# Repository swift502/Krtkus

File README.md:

# Krtkus

> [!WARNING]
> Krtkus has been succeeded by [Krteq](https://github.com/swift502/Krteq), a much more complete design that's also easier to build. I recommend you check it out instead!

An extended 5x12 keyboard with 2 extra keys. The design is intended for ortho layouts with a shifted number row, allowing for the placement of the delete and tilde keys above their usual spots. PCBs are designed in Kicad, case in Blender.

- Low profile
    - Kailh Choc V1
    - Gateron KS-27/KS-33
- QMK/VIA compatible
- Tray mount
- 3D printed case with a 7 degree tilt
- 236mm × 122mm × 30mm

Connecting the keyboard to [usevia.app](https://usevia.app) requires manually uploading the [design file](production/krtkus_via.json) in the design tab.

## Parts

- One of the PCBs:
    - [Choc V1](production/pcb_choc_v1)
    - [KS-33](production/pcb_ks_33)
- Case: 
    - [STL file](production/krtkus_case.stl)
- Arduino Pro Micro
- 61 SMD diodes
- 61 switches
- 61 keycaps
- 5 M2x6mm screws

#### Optional:

- 90 degree Micro-USB cable
- Rubber feet

## Room for improvement

- Spacebar stabilizer
- Num/Caps indicators
- LED matrix
- Hotswap version
- Standard USB port orientation
- Protect the MCU against dust

All of the above have been addressed by the successor [Krteq](https://github.com/swift502/Krteq).

## My builds

| Board | Keycaps | Switches | Case | Firmware |
| --- | --- | --- | --- | --- |
|  | MBK Legend Ergo/Ortho | Choc V1 Brown | Black Resin | Caterina |
|  | Keychron LSA ABS | KS-33 Brown | Black Resin | Caterina |
|  | Keychron LSA ABS | KS-33 Red | 9600 Resin | Caterina (Legacy) |
|  | Dell AT101W | KS-33 Banana | [Krtkus Retro](https://github.com/swift502/KrtkusRetro) | Caterina |

## QMK

Standard QMK setup except for `"tap_keycode_delay": 40`, which fixes ignored taps in some games where input scanning is tied to frame rate. To the best of my knowledge, keeping this value above 33ms (30fps) should cover all edge cases.

### Documentation

- `info.json` reference: https://docs.qmk.fm/reference_info_json
- Keycodes: https://docs.qmk.fm/keycodes

### Compiling (Windows)

- Python: https://www.python.org/
- MSYS: https://msys.qmk.fm
- Toolbox: https://qmk.fm/toolbox

Run the compile script:

```sh
python qmk_compile.py
```

### Resetting

Once the firmware is flashed, it provides key combinations to enter bootloader or clear the keyboard's persistent storage.

- <kbd>LShift</kbd> + <kbd>RShift</kbd> + <kbd>B</kbd> - Puts the keyboard into bootloader mode for flashing
- <kbd>LShift</kbd> + <kbd>RShift</kbd> + <kbd>C</kbd> - Clears EEPROM and reverts to the default keymap

## Kicad 8

### Libraries

Below is a list libraries included in the project. These libraries are not licensed under CC0. Please refer to each specific library for licensing details.

- [Scotto Kicad](https://github.com/joe-scotto/scottokeebs/tree/main/Extras/ScottoKicad)
- [MX V2](https://github.com/ai03-2725/MX_V2)
- [Gateron 3D models](https://www.gateron.com/pages/3d)

### Switch grid

| Unit | Offset |
| --- | --- |
| Switch | 19.05 |
| Switch 4 | 4.7625 |
| Switch 16 | 1.190625 |
| Switch 64 | 0.29765625 |

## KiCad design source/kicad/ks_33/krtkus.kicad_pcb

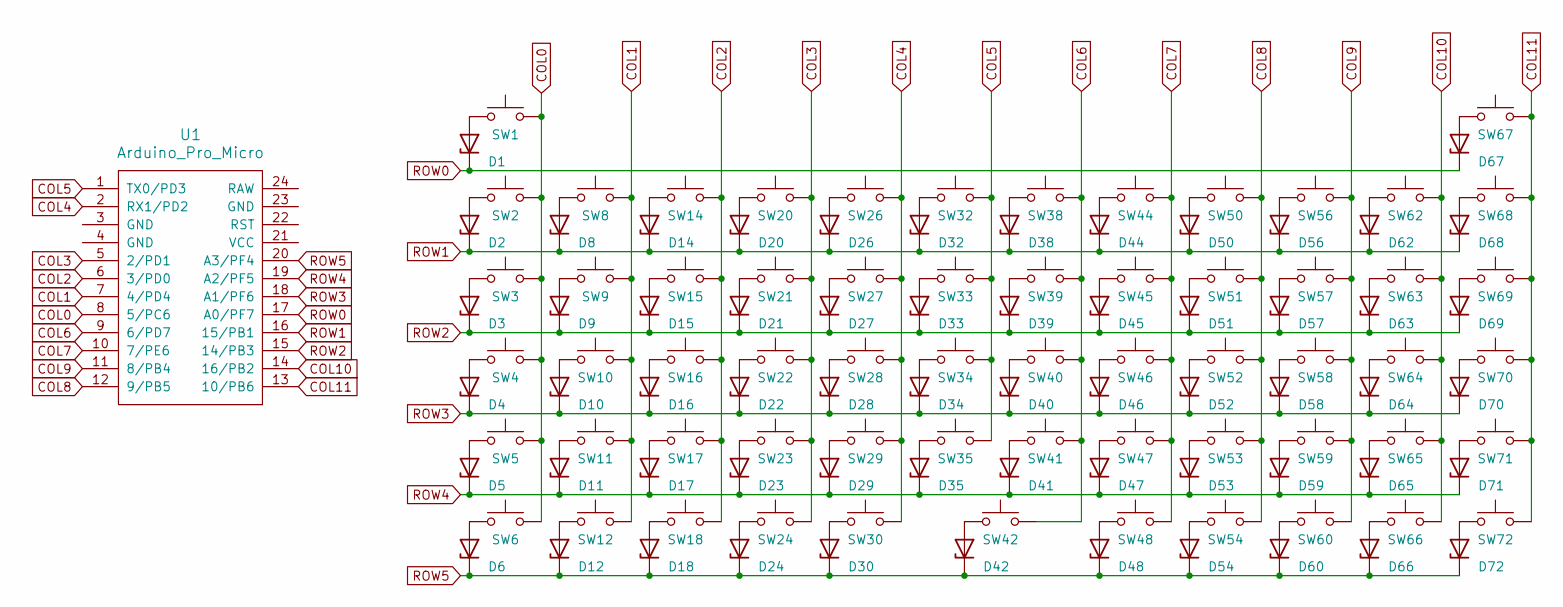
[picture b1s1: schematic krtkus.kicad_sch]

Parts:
D1, D2, D3, D4, D5, D6, D8, D9, D10, D11, D12, D14, D15, D16, D17, D18, D20, D21, D22, D23, D24, D26, D27, D28, D29, D30, D32, D33, D34, D35, D38, D39, D40, D41, D42, D44, D45, D46, D47, D48, D50, D51, D52, D53, D54, D56, D57, D58, D59, D60, D62, D63, D64, D65, D66, D67, D68, D69, D70, D71, D72: 1N47xxA; Diode_SOD-123
SW1, SW2, SW3, SW4, SW5, SW6, SW8, SW9, SW10, SW11, SW12, SW14, SW15, SW16, SW17, SW18, SW20, SW21, SW22, SW23, SW24, SW26, SW27, SW28, SW29, SW30, SW32, SW33, SW34, SW35, SW38, SW39, SW40, SW41, SW42, SW44, SW45, SW46, SW47, SW48, SW50, SW51, SW52, SW53, SW54, SW56, SW57, SW58, SW59, SW60, SW62, SW63, SW64, SW65, SW66, SW67, SW68, SW69, SW70, SW71, SW72: Push; Gateron-KS33-Solderable-1U-Tight
U1: Arduino_Pro_Micro

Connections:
COL0: SW1.2, SW2.2, SW3.2, SW4.2, SW5.2, SW6.2, U1.8 (5/PC6)
COL1: SW8.2, SW9.2, SW10.2, SW11.2, SW12.2, U1.7 (4/PD4)
COL2: SW14.2, SW15.2, SW16.2, SW17.2, SW18.2, U1.6 (3/PD0)
COL3: SW20.2, SW21.2, SW22.2, SW23.2, SW24.2, U1.5 (2/PD1)
COL4: SW26.2, SW27.2, SW28.2, SW29.2, SW30.2, U1.2 (RX1/PD2)
COL5: SW32.2, SW33.2, SW34.2, SW35.2, U1.1 (TX0/PD3)
COL6: SW38.2, SW39.2, SW40.2, SW41.2, SW42.2, U1.9 (6/PD7)
COL7: SW44.2, SW45.2, SW46.2, SW47.2, SW48.2, U1.10 (7/PE6)
COL8: SW50.2, SW51.2, SW52.2, SW53.2, SW54.2, U1.12 (9/PB5)
COL9: SW56.2, SW57.2, SW58.2, SW59.2, SW60.2, U1.11 (8/PB4)
COL10: SW62.2, SW63.2, SW64.2, SW65.2, SW66.2, U1.14 (16/PB2)
COL11: SW67.2, SW68.2, SW69.2, SW70.2, SW71.2, SW72.2, U1.13 (10/PB6)
unnamed: D1.2 (A), SW1.1
unnamed: D2.2 (A), SW2.1
unnamed: D3.2 (A), SW3.1
unnamed: D4.2 (A), SW4.1
unnamed: D5.2 (A), SW5.1
unnamed: D6.2 (A), SW6.1
unnamed: D8.2 (A), SW8.1
unnamed: D9.2 (A), SW9.1
unnamed: D10.2 (A), SW10.1
unnamed: D11.2 (A), SW11.1
unnamed: D12.2 (A), SW12.1
unnamed: D14.2 (A), SW14.1
unnamed: D15.2 (A), SW15.1
unnamed: D16.2 (A), SW16.1
unnamed: D17.2 (A), SW17.1
unnamed: D18.2 (A), SW18.1
unnamed: D20.2 (A), SW20.1
unnamed: D21.2 (A), SW21.1
unnamed: D22.2 (A), SW22.1
unnamed: D23.2 (A), SW23.1
unnamed: D24.2 (A), SW24.1
unnamed: D26.2 (A), SW26.1
unnamed: D27.2 (A), SW27.1
unnamed: D28.2 (A), SW28.1
unnamed: D29.2 (A), SW29.1
unnamed: D30.2 (A), SW30.1
unnamed: D32.2 (A), SW32.1
unnamed: D33.2 (A), SW33.1
unnamed: D34.2 (A), SW34.1
unnamed: D35.2 (A), SW35.1
unnamed: D38.2 (A), SW38.1
unnamed: D39.2 (A), SW39.1
unnamed: D40.2 (A), SW40.1
unnamed: D41.2 (A), SW41.1
unnamed: D42.2 (A), SW42.1
unnamed: D44.2 (A), SW44.1
unnamed: D45.2 (A), SW45.1
unnamed: D46.2 (A), SW46.1
unnamed: D47.2 (A), SW47.1
unnamed: D48.2 (A), SW48.1
unnamed: D50.2 (A), SW50.1
unnamed: D51.2 (A), SW51.1
unnamed: D52.2 (A), SW52.1
unnamed: D53.2 (A), SW53.1
unnamed: D54.2 (A), SW54.1
unnamed: D56.2 (A), SW56.1
unnamed: D57.2 (A), SW57.1
unnamed: D58.2 (A), SW58.1
unnamed: D59.2 (A), SW59.1
unnamed: D60.2 (A), SW60.1
unnamed: D62.2 (A), SW62.1
unnamed: D63.2 (A), SW63.1
unnamed: D64.2 (A), SW64.1
unnamed: D65.2 (A), SW65.1
unnamed: D66.2 (A), SW66.1
unnamed: D67.2 (A), SW67.1
unnamed: D68.2 (A), SW68.1
unnamed: D69.2 (A), SW69.1
unnamed: D70.2 (A), SW70.1
unnamed: D71.2 (A), SW71.1
unnamed: D72.2 (A), SW72.1
ROW0: D1.1 (K), D67.1 (K), U1.17 (A0/PF7)
ROW1: D2.1 (K), D8.1 (K), D14.1 (K), D20.1 (K), D26.1 (K), D32.1 (K), D38.1 (K), D44.1 (K), D50.1 (K), D56.1 (K), D62.1 (K), D68.1 (K), U1.16 (15/PB1)
ROW2: D3.1 (K), D9.1 (K), D15.1 (K), D21.1 (K), D27.1 (K), D33.1 (K), D39.1 (K), D45.1 (K), D51.1 (K), D57.1 (K), D63.1 (K), D69.1 (K), U1.15 (14/PB3)
ROW3: D4.1 (K), D10.1 (K), D16.1 (K), D22.1 (K), D28.1 (K), D34.1 (K), D40.1 (K), D46.1 (K), D52.1 (K), D58.1 (K), D64.1 (K), D70.1 (K), U1.18 (A1/PF6)
ROW4: D5.1 (K), D11.1 (K), D17.1 (K), D23.1 (K), D29.1 (K), D35.1 (K), D41.1 (K), D47.1 (K), D53.1 (K), D59.1 (K), D65.1 (K), D71.1 (K), U1.19 (A2/PF5)
ROW5: D6.1 (K), D12.1 (K), D18.1 (K), D24.1 (K), D30.1 (K), D42.1 (K), D48.1 (K), D54.1 (K), D60.1 (K), D66.1 (K), D72.1 (K), U1.20 (A3/PF4)

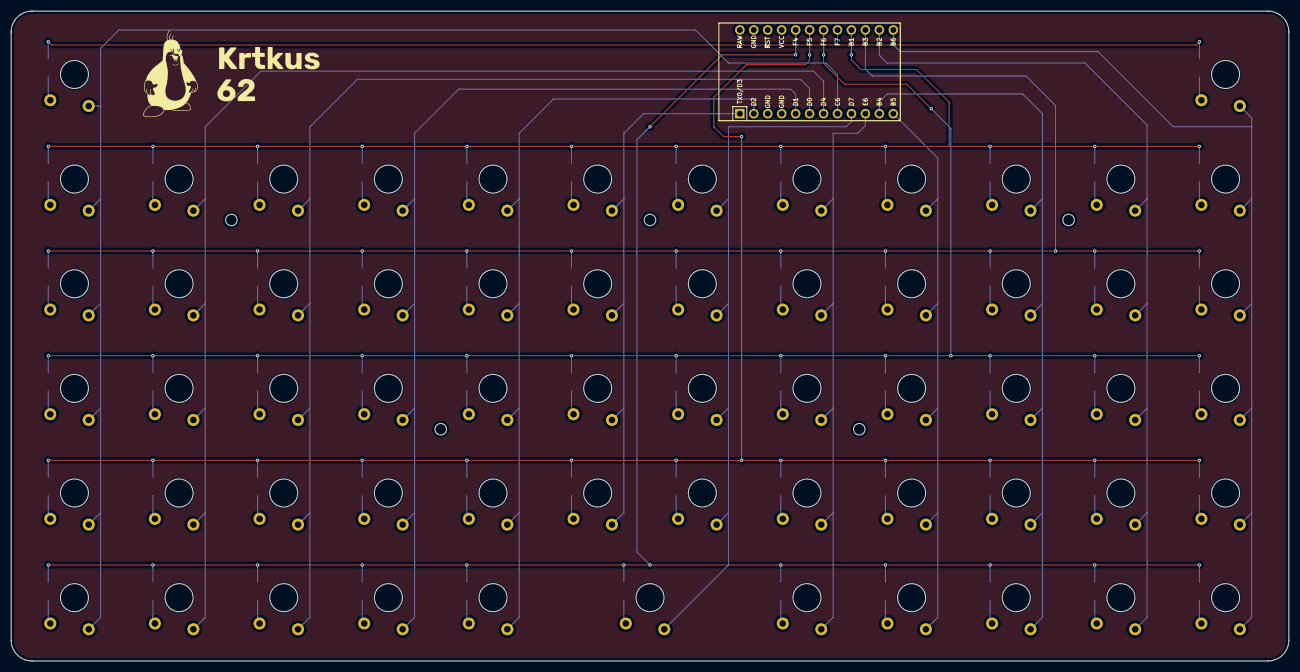
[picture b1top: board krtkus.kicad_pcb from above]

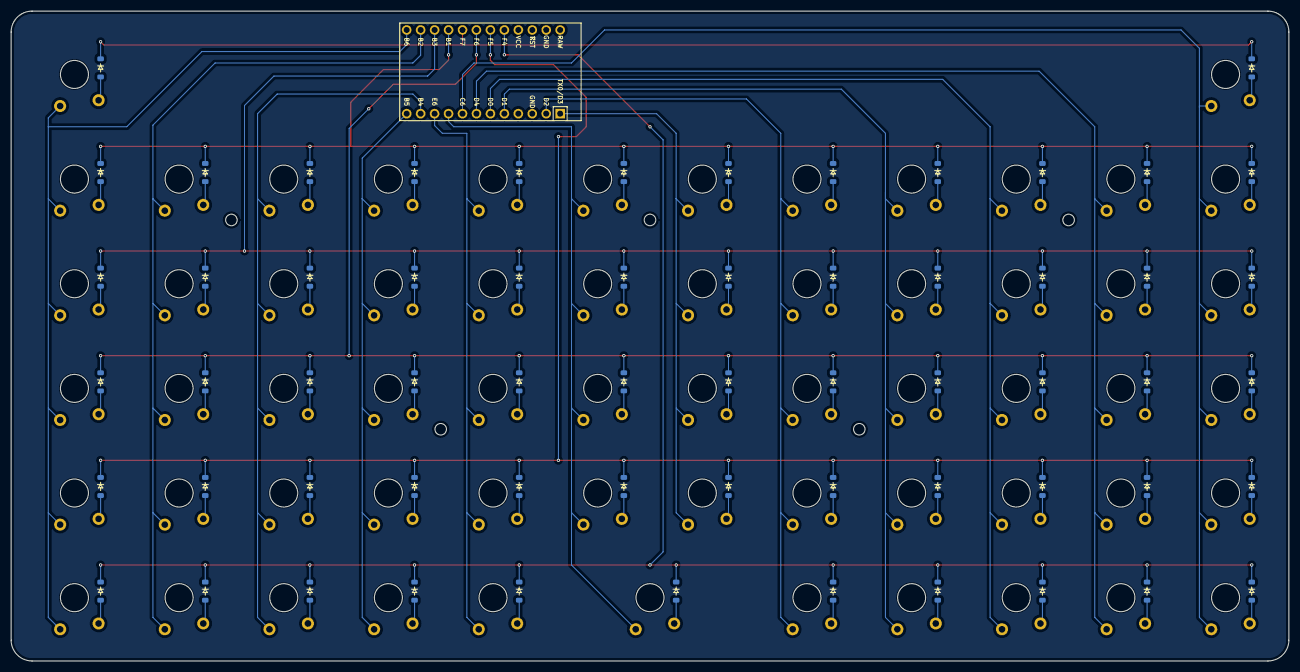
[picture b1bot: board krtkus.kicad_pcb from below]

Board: 2 copper layers, 232.6 x 118.3 mm, 123 parts (61 on the bottom side), 79 nets.

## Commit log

2024-04-01 init
2024-04-01 Rename
2024-04-01 diodes
2024-04-02 traces
2024-04-02 pi traces
2024-04-02 outline
2024-04-02 icon
2024-04-02 filled zone
2024-04-02 gitignore
2024-10-14 S67 fix
2024-10-14 path tweaks
2024-10-14 tweak
2024-10-15 scottokicad
2024-10-15 paths
2024-10-15 spacebar
2024-10-15 case v1
2024-10-15 case v2
2024-10-16 case v3
2024-10-16 holes rework, case v4
2024-10-16 cleanup
2024-10-16 case origin
2024-10-16 production edits
2024-10-16 model
2024-10-17 tweaks
2024-10-18 production, readme
2024-10-18 remove switch labels
2024-10-18 through hole
2024-10-19 case update
2024-10-19 readme
2024-10-19 images
2024-10-19 reaadme
2024-10-21 qmk init
2024-10-21 space bar
2024-10-21 qmk compile
2024-10-22 layout tweak
2024-10-30 name
2024-10-30 firmware update
2024-10-30 keymap update
2024-10-30 project structure
2024-10-31 naming
2024-10-31 layout
2024-10-31 case supports fix
2024-10-31 keymap
2024-11-02 image res
2024-11-02 Create LICENSE
2024-11-02 thumb
2024-11-02 thumb 2
2024-11-02 Update LICENSE
2024-11-03 gateron firmware
2024-11-03 case export
2024-11-06 schematic images
2024-11-08 firmware fix bruh moment
2024-11-09 unification
2024-11-09 file name
2024-11-16 ks-33 footprint tweaks
2024-11-22 logo edits
2024-11-23 clickable images
2024-12-01 keymap update, custom VIA keycode
2024-12-01 ctrl vol
2024-12-01 build
2024-12-02 refactor
2024-12-02 bootloader fix, keymap update
2024-12-03 soft reset
2024-12-05 indentation
2024-12-30 include legacy ks pinout
2025-02-11 hold_on_other_key_press
2025-02-11 sort
2025-03-03 firmware
2025-03-07 compile script
2025-03-07 Live compile output
2025-03-07 compile script name
2025-03-07 libraries refactor
2025-03-07 docs
2025-03-07 lib licensing
2025-03-07 licensing 2
2025-03-07 licensing 3
2025-03-07 compiler bootloader override
2025-03-07 License
2025-03-07 compiler tweaks
2025-03-07 comments
2025-03-07 compiler cleanup
2025-03-10 formatting
2025-03-10 qmk refactor, firmware build
2025-03-10 legacy compile parameter
2025-03-17 qmk update
2025-03-19 thumb update
2025-03-20 Revert
2025-03-21 color temperature
2025-03-21 colors 2
2025-04-12 compiler questionary
2025-04-12 compiler early exits
2025-04-14 qmk update, compile
2025-04-14 build task
2025-04-19 global paths
2025-04-19 streamlining
2025-04-21 compiler refactor, cleanup
2025-04-24 compiler args, tasks
2025-05-20 build 5
2025-05-30 case cleanup
2025-06-01 tap_keycode_delay
2025-06-01 krt_vol hold
2025-06-01 krt_vol optimization
2025-06-02 image update
2025-06-13 disable mousekey, better compiler path handling
2025-06-13 KRT_VOL consistency
2025-06-13 remove bootmagic
2025-06-14 wsl2 compile
2025-06-20 QK_CLEAR_EEPROM source parity
2025-06-20 shorthand codes
2025-06-26 via json name
2025-06-27 keyboard layout editor file
2025-07-10 remove layout colors
2025-07-10 remove layout font size
2025-07-22 kle cleanup
2025-07-31 Input disable toggle
2025-07-31 6 layers
2025-08-02 enable repeat presses on enter
2025-10-24 builds
2025-10-27 keymap edit
2025-10-29 qmk layout fix
2025-11-03 logo rework
2025-11-04 logo cleanup
2025-11-04 pcb build update
2025-11-10 tasks
2025-11-12 default keymap
2025-11-14 script cleanup
2025-11-16 builds update
2025-11-16 links fix
2025-12-28 svg cleanup
2025-12-28 svg cleanup 2
